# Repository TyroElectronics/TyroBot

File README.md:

# TyroBot
copyright :copyright: 2016 Tyro Electronics </br>
GPL General Public License 3.0</br>
https://tyroelectronics.com

## Build
Complete building Instructions coming soon!
## Code
Full library documentation coming soon!
## Repeat
Customize your TyroBot!(coming soon)

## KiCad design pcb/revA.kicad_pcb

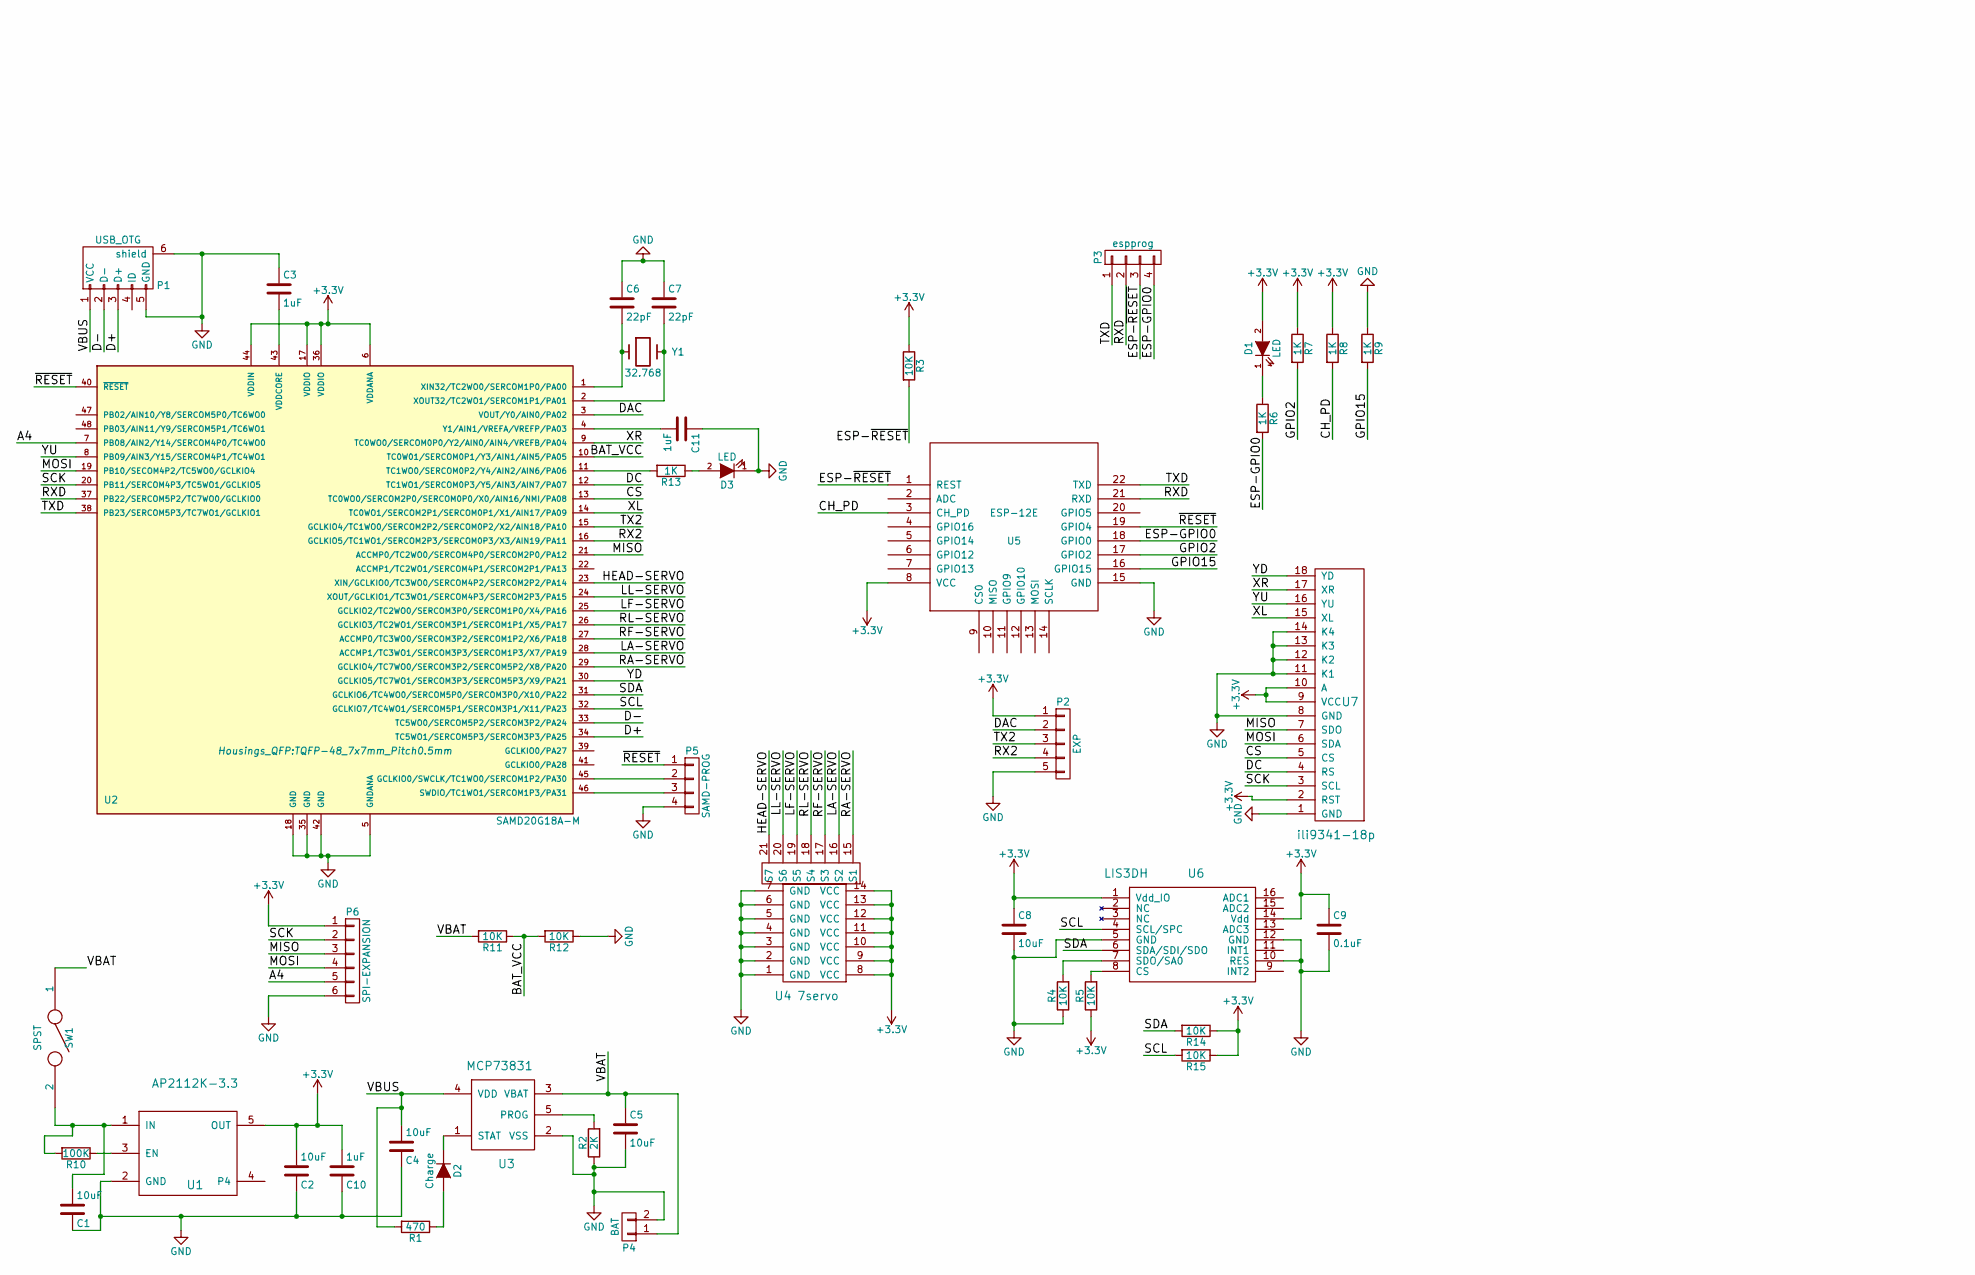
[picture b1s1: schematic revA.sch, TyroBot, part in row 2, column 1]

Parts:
C1, C2, C4: 10uF; C_0805
C3: 1uF; R_0805
C5, C8: 10uF; R_0805
C6, C7: 22pF; R_0805
C9: 0.1uF; R_0805
C10, C11: 1uF; C_0805
D1, D3: LED; LED_0805
D2: Charge; LED_0805
P1: USB_OTG; micro-usb-fci
P2: EXP; JST_PH_B5B-PH-SM4-TB_05x2.00mm_Straight
P3: espprog; Pin_Header_Straight_1x04_Pitch2.54mm
P4: BAT; JST2
P5: SAMD-PROG; progatsam
P6: SPI-EXPANSION; JST_PH_B6B-PH-SM4-TB_06x2.00mm_Straight
R1: 470; R_0805
R2: 2K; R_0805
R3, R4, R5, R11, R12, R14, R15: 10K; R_0805
R6, R7, R8, R9, R13: 1K; R_0805
R10: 100K; R_0805
SW1: SPST; eg1224
U1: AP2112K-3.3; SOT-23-5
U2: SAMD20G18A-M; TQFP-48_7x7mm_Pitch0.5mm
U3: MCP73831; SOT-23-5
U4: 7servo; servo7
U5: ESP-12E
U6: LIS3DH; LGA-16-3x3
U7: ili9341-18p; 18p-ili9341
Y1: 32.768; FC-135

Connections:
+3V3: C2.2, C8.1, C9.1, C10.2, D1.2 (A), P2.1, P6.1, R3.1, R5.1, R7.1, R8.1, R14.1, R15.1, U1.5 (OUT), U2.6 (VDDANA), U2.17 (VDDIO), U2.36 (VDDIO), U2.44 (VDDIN), U4.8 (VCC), U4.9 (VCC), U4.10 (VCC), U4.11 (VCC), U4.12 (VCC), U4.13 (VCC), U4.14 (VCC), U5.8 (VCC), U6.1 (Vdd_IO), U6.14 (Vdd), U7.2 (RST), U7.9 (VCC), U7.10 (A)
/A4: P6.5, U2.7 (PB08/AIN2/Y14/SERCOM4P0/TC4WO0)
/BAT_VCC: R11.1, R12.2, U2.10 (TC0W01/SERCOM0P1/Y3/AIN1/AIN5/PA05)
/CH_PD: R8.2, U5.3 (CH_PD)
/CS: U2.13 (TC0WO0/SERCOM2P0/SERCOM0P0/X0/AIN16/NMI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), U7.5 (CS)
/D+: P1.3 (D+), U2.34 (TC5WO1/SERCOM5P3/SERCOM3P3/PA25)
/D-: P1.2 (D-), U2.33 (TC5WO0/SERCOM5P2/SERCOM3P2/PA24)
/DAC: P2.2, U2.3 (VOUT/Y0/AIN0/PA02)
/DC: U2.12 (TC1WO1/SERCOM0P3/Y5/AIN3/AIN7/PA07), U7.4 (RS)
/ESP-GPIO0: P3.4, R6.2, U5.18 (GPIO0)
/ESP-~RESET: P3.3, R3.2, U5.1 (REST)
/GPIO2: R7.2, U5.17 (GPIO2)
/GPIO15: R9.2, U5.16 (GPIO15)
/HEAD-SERVO: U2.23 (XIN/GCLKIO0/TC3WO0/SERCOM4P2/SERCOM2P2/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), U4.21 (S7)
/LA-SERVO: U2.28 (ACCMP1/TC3WO1/SERCOM3P3/SERCOM1P3/X7/PA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), U4.16 (S2)
/LF-SERVO: U2.25 (GCLKIO2/TC2WO0/SERCOM3P0/SERCOM1P0/X4/P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), U4.19 (S5)
/LL-SERVO: U2.24 (XOUT/GCLKIO1/TC3WO1/SERCOM4P3/SERCOM2P3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), U4.20 (S6)
/MISO: P6.3, U2.21 (ACCMP0/TC2WO0/SERCOM4P0/SERCOM2P0/PA12), U7.7 (SDO)
/MOSI: P6.4, U2.19 (PB10/SECOM4P2/TC5WO0/GCLKIO4), U7.6 (SDA)
/RA-SERVO: U2.29 (GCLKIO4/TC7WO0/SERCOM3P2/SERCOM5P2/X8/P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), U4.15 (S1)
/RF-SERVO: U2.27 (ACCMP0/TC3WO0/SERCOM3P2/SERCOM1P2/X6/PA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), U4.17 (S3)
/RL-SERVO: U2.26 (GCLKIO3/TC2WO1/SERCOM3P1/SERCOM1P1/X5/P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), U4.18 (S4)
/RX2: P2.4, U2.16 (GCLKIO5/TC1WO1/SERCOM2P3/SERCOM0P3/X3/A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)
/RXD: P3.2, U2.37 (PB22/SERCOM5P2/TC7WO0/GCLKIO0), U5.21 (RXD)
/SCK: P6.2, U2.20 (PB11/SERCOM4P3/TC5WO1/GCLKIO5), U7.3 (SCL)
/SCL: R15.2, U2.32 (GCLKIO7/TC4WO1/SERCOM5P1/SERCOM3P1/X11/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), U6.4 (SCL/SPC)
/SDA: R14.2, U2.31 (GCLKIO6/TC4WO0/SERCOM5P0/SERCOM3P0/X10/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), U6.6 (SDA/SDI/SDO)
/TX2: P2.3, U2.15 (GCLKIO4/TC1WO0/SERCOM2P2/SERCOM0P2/X2/A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)
/TXD: P3.1, U2.38 (PB23/SERCOM5P3/TC7WO1/GCLKIO1), U5.22 (TXD)
/VBAT: C5.1, P4.1, R11.2, SW1.1, U3.3 (VBAT)
/VBUS: C4.2, P1.1 (VCC), R1.2, U3.4 (VDD)
/XL: U2.14 (TC0WO1/SERCOM2P1/SERCOM0P1/X1/AIN17/PA09), U7.15 (XL)
/XR: U2.9 (TC0WO0/SERCOM0P0/Y2/AIN0/AIN4/VREFB/PA04), U7.17 (XR)
/YD: U2.30 (GCLKIO5/TC7WO1/SERCOM3P3/SERCOM5P3/X9/P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), U7.18 (YD)
/YU: U2.8 (PB09/AIN3/Y15/SERCOM4P1/TC4WO1), U7.16 (YU)
/~RESET: P5.1, U2.40 (~RESET~), U5.19 (GPIO4)
GND: C1.1, C2.1, C3.1, C4.1, C5.2, C6.1, C7.1, C8.2, C9.2, C10.1, C11.1, D3.1 (K), P1.5 (GND), P1.6 (shield), P2.5, P4.2, P5.4, P6.6, R2.1, R4.1, R9.1, R12.1, U1.2 (GND), U2.5 (GNDANA), U2.18 (GND), U2.35 (GND), U2.42 (GND), U3.2 (VSS), U4.1 (GND), U4.2 (GND), U4.3 (GND), U4.4 (GND), U4.5 (GND), U4.6 (GND), U4.7 (GND), U5.15 (GND), U6.5 (GND), U6.10 (RES), U6.12 (GND), U7.1 (GND), U7.8 (GND), U7.11 (K1), U7.12 (K2), U7.13 (K3), U7.14 (K4)
unnamed: C1.2, R10.2, SW1.2, U1.1 (IN)
unnamed: C3.2, U2.43 (VDDCORE)
unnamed: C6.2, U2.1 (XIN32/TC2WO0/SERCOM1P0/PA00), Y1.1
unnamed: C7.2, U2.2 (XOUT32/TC2WO1/SERCOM1P1/PA01), Y1.2
unnamed: C11.2, U2.4 (Y1/AIN1/VREFA/VREFP/PA03)
unnamed: D1.1 (K), R6.1
unnamed: D2.1 (K), U3.1 (STAT)
unnamed: D2.2 (A), R1.1
unnamed: D3.2 (A), R13.1
unnamed: P5.2, U2.45 (GCLKIO0/SWCLK/TC1WO0/SERCOM1P2/PA30)
unnamed: P5.3, U2.46 (SWDIO/TC1WO1/SERCOM1P3/PA31)
unnamed: R2.2, U3.5 (PROG)
unnamed: R4.2, U6.7 (SDO/SA0)
unnamed: R5.2, U6.8 (CS)
unnamed: R10.1, U1.3 (EN)
unnamed: R13.2, U2.11 (TC1WO0/SERCOM0P2/Y4/AIN2/AIN6/PA06)

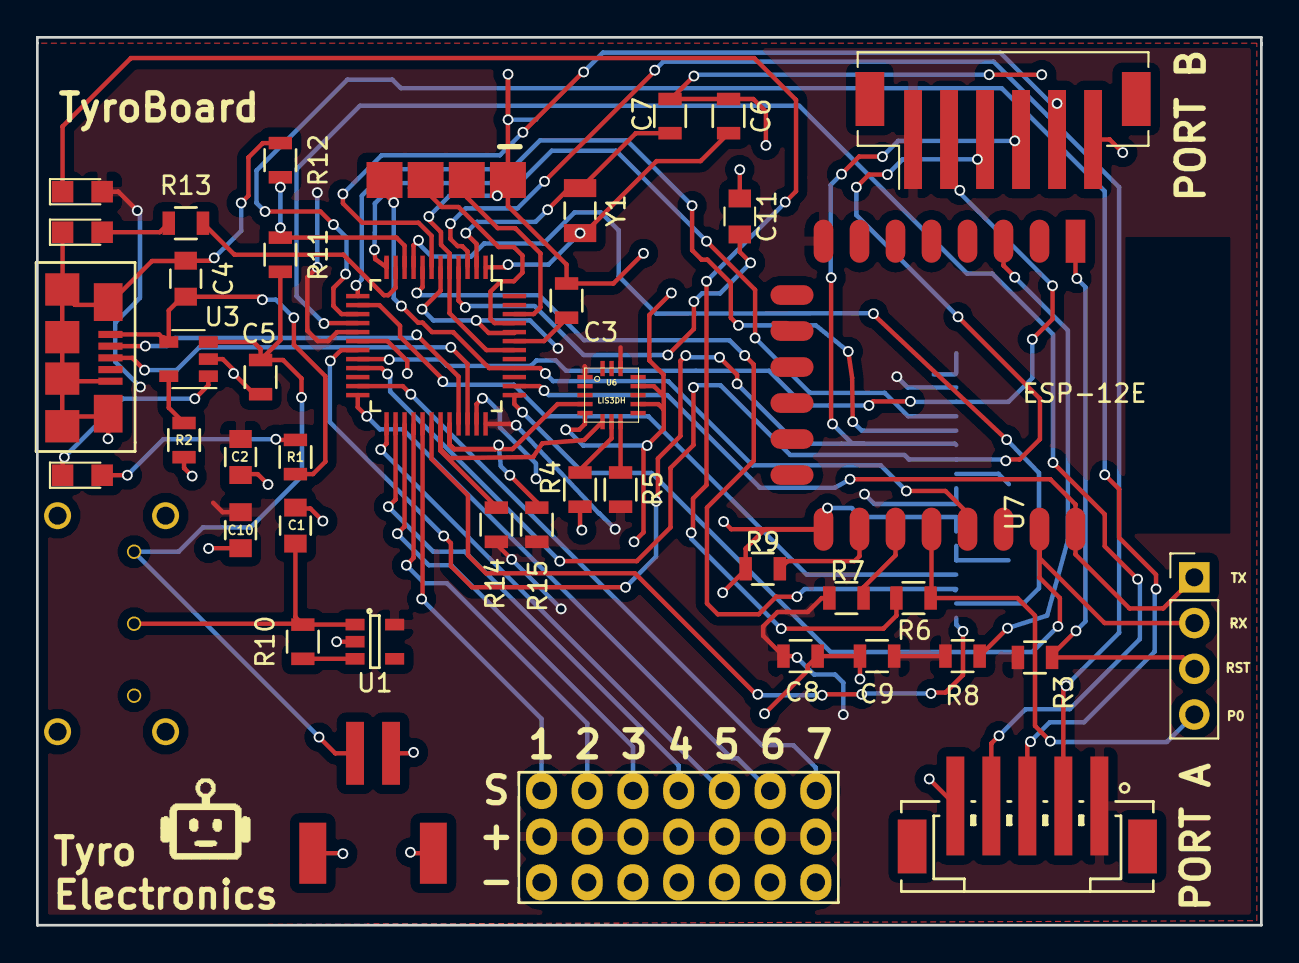
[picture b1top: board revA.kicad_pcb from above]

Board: 2 copper layers, 68.0 x 49.3 mm, 45 parts (1 on the bottom side), 53 nets.

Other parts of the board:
tyrobotlogo: tyrobotlogo

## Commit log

2017-07-07 Added files :us:
2017-07-08 Update to walk sequence
2017-08-02 added pcb
2017-08-06 stronger torso, better calibration
2017-08-15 put in library form
2017-09-08 Updated PCB to the version shipping to kickstarter backers :+1:
2017-10-11 fixes :bowtie:
2017-11-12 shipped kickstarter software
2017-11-13 added 3d model package
2017-11-16 more fixes :angry:
2017-11-19 cadddd.
2017-11-19 parts
